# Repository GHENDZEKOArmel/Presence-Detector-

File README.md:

# Infrared Presence Detector – Electronic Design (KiCad)

##  Description
This project focuses on the design of an **active infrared presence detector** based on a
**fully analog signal processing chain**.

The system emits a modulated infrared signal, detects the reflection caused by a nearby object
(human presence), and processes the received signal in order to generate a **usable logic output**.

The project was designed and simulated using **KiCad**, with an **academic and educational purpose**,
following a modular architecture inspired by industrial detection systems.

---

##  Operating Principle

1. An **infrared emitting diode (IR LED)** generates a modulated IR signal.
2. A **photodiode receiver** detects the reflected infrared signal.
3. The received current is converted into a voltage (TIA).
4. A **band-pass filter** rejects ambient noise.
5. The signal is **amplified**.
6. A **peak detector** extracts the signal envelope.
7. A **comparator** compares the signal with an adjustable threshold.
8. A **logic output** indicates the detected presence.

### Functional blocks

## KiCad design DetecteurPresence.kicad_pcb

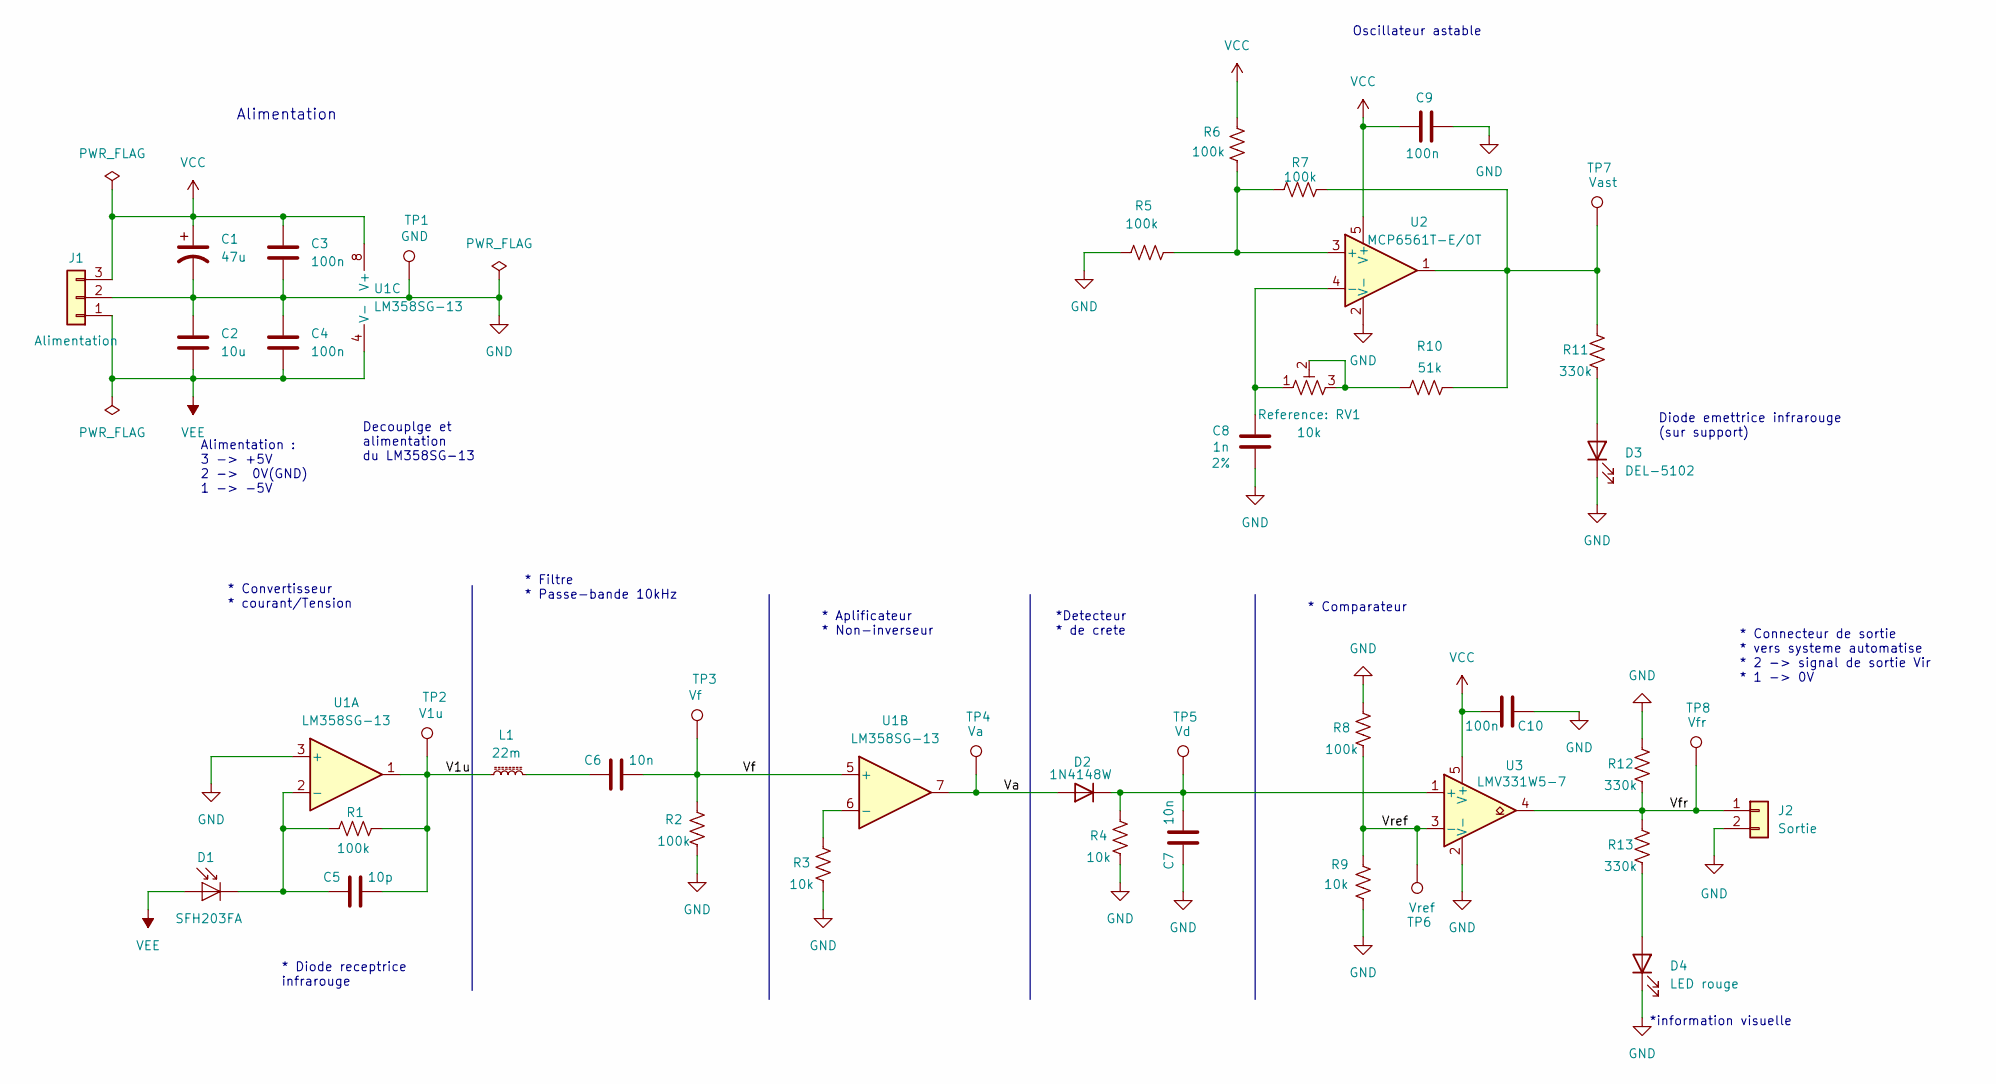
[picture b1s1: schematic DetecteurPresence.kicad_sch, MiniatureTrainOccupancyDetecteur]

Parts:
C1: 47u; CP_Elec_5x5.4
C2: 10u; C_0805_2012Metric_Pad1.18x1.45mm_HandSolder
C3, C4, C9, C10: 100n; C_0805_2012Metric_Pad1.18x1.45mm_HandSolder
C5: 10p; C_0805_2012Metric_Pad1.18x1.45mm_HandSolder
C6, C7: 10n; C_0805_2012Metric_Pad1.18x1.45mm_HandSolder
C8: 1n; C_0805_2012Metric_Pad1.18x1.45mm_HandSolder; Tolerance 2%
D1: SFH203FA; PinSocket_1x02_P2.54mm_Vertical
D2: 1N4148W; D_SOD-123F
D3: DEL-5102; PinSocket_1x02_P2.54mm_Vertical
D4: LED rouge; LED_0805_2012Metric_Pad1.15x1.40mm_HandSolder
J1: Alimentation; PinHeader_1x03_P2.54mm_Vertical
J2: Sortie; PinHeader_1x02_P2.54mm_Vertical
L1: 22m; L_Radial_D7.8mm_P5.00mm_Fastron_07HCP
R1, R2, R5, R6, R7, R8: 100k; R_0805_2012Metric_Pad1.20x1.40mm_HandSolder
R3, R4, R9: 10k; R_0805_2012Metric_Pad1.20x1.40mm_HandSolder
R10: 51k; R_0805_2012Metric_Pad1.20x1.40mm_HandSolder
R11, R12, R13: 330k; R_0805_2012Metric_Pad1.20x1.40mm_HandSolder
RV1: 10k; Potentiometer_Bourns_TC33X_Vertical
TP1: GND; TestPoint_Keystone_5019_Miniature
TP2: V1u; TestPoint_Keystone_5019_Miniature
TP3: Vf; TestPoint_Keystone_5019_Miniature
TP4: Va; TestPoint_Keystone_5019_Miniature
TP5: Vd; TestPoint_Keystone_5019_Miniature
TP6: Vref; TestPoint_Keystone_5019_Miniature
TP7: Vast; TestPoint_Keystone_5019_Miniature
TP8: Vfr; TestPoint_Keystone_5019_Miniature
U1: LM358SG-13; SOIC-8_5.3x6.2mm_P1.27mm
U2: MCP6561T-E/OT; SOT-23-5_HandSoldering
U3: LMV331W5-7; SOT-23-5

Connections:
/V1u: C5.2, L1.1, R1.2, TP2.1, U1.1
/Va: D2.2 (A), TP4.1, U1.7
/Vf: C6.2, R2.2, TP3.1, U1.5 (+)
/Vfr: J2.1, R12.1, R13.2, TP8.1, U3.4
/Vref: R8.1, R9.1, TP6.1, U3.3 (-)
GND: C1.2, C2.1, C3.2, C4.1, C7.1, C8.2, C9.1, C10.1, D3.1 (K), D4.1 (K), J1.2, J2.2, R2.1, R3.1, R4.1, R5.1, R8.2, R9.2, R12.2, TP1.1, U1.3 (+), U2.2 (V-), U3.2 (V-)
unnamed: C6.1, L1.2
unnamed: C5.1, D1.1 (K), R1.1, U1.2 (-)
unnamed: C7.2, D2.1 (K), R4.2, TP5.1, U3.1 (+)
unnamed: D3.2 (A), R11.1
unnamed: D4.2 (A), R13.1
unnamed: R10.1, RV1.2, RV1.3
unnamed: R7.2, R10.2, R11.2, TP7.1, U2.1
unnamed: R3.2, U1.6 (-)
unnamed: R5.2, R6.1, R7.1, U2.3 (+)
unnamed: C8.1, RV1.1, U2.4 (-)
VCC: C1.1, C3.1, C9.2, C10.2, J1.3, R6.2, U1.8 (V+), U2.5 (V+), U3.5 (V+)
VEE: C2.2, C4.2, D1.2 (A), J1.1, U1.4 (V-)

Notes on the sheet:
Alimentation
* Diode receptrice infrarouge
Decouplge et alimentation du LM358SG-13
*information visuelle
Diode emettrice infrarouge (sur support)
* Comparateur
*Detecteur * de crete
* Convertisseur * courant/Tension
Alimentation : 3 -> +5V 2 -> 0V(GND) 1 -> -5V
* Filtre * Passe-bande 10kHz
* Aplificateur * Non-inverseur
Oscillateur astable
* Connecteur de sortie * vers systeme automatise * 2 -> signal de sortie Vir * 1 -> 0V

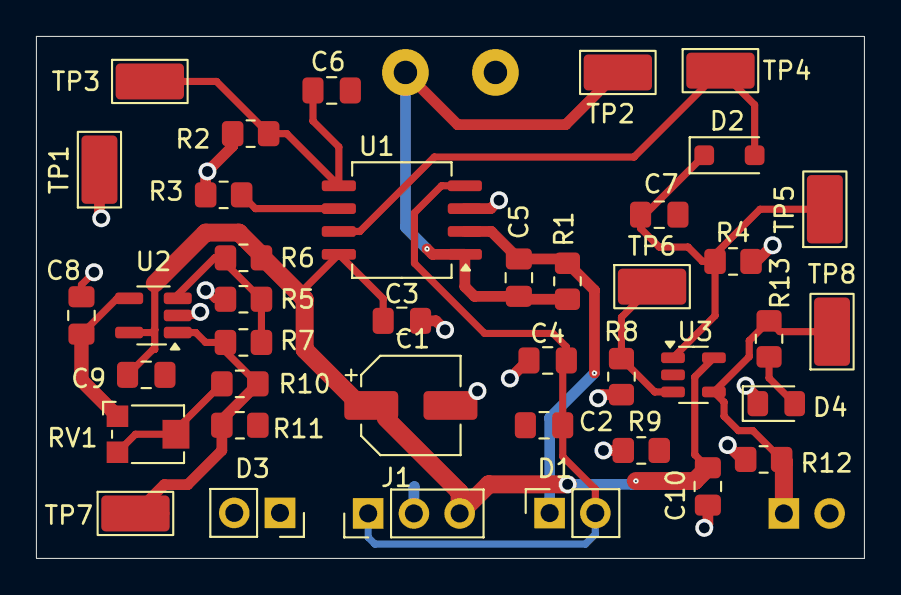
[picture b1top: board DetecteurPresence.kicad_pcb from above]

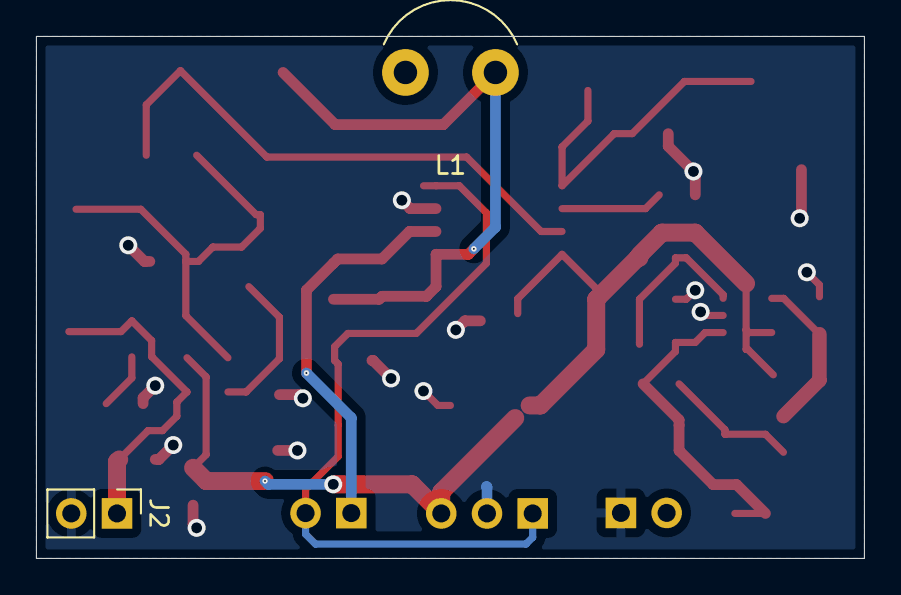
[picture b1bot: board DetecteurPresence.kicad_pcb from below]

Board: 2 copper layers, 46.0 x 29.0 mm, 42 parts (2 on the bottom side), 18 nets.
